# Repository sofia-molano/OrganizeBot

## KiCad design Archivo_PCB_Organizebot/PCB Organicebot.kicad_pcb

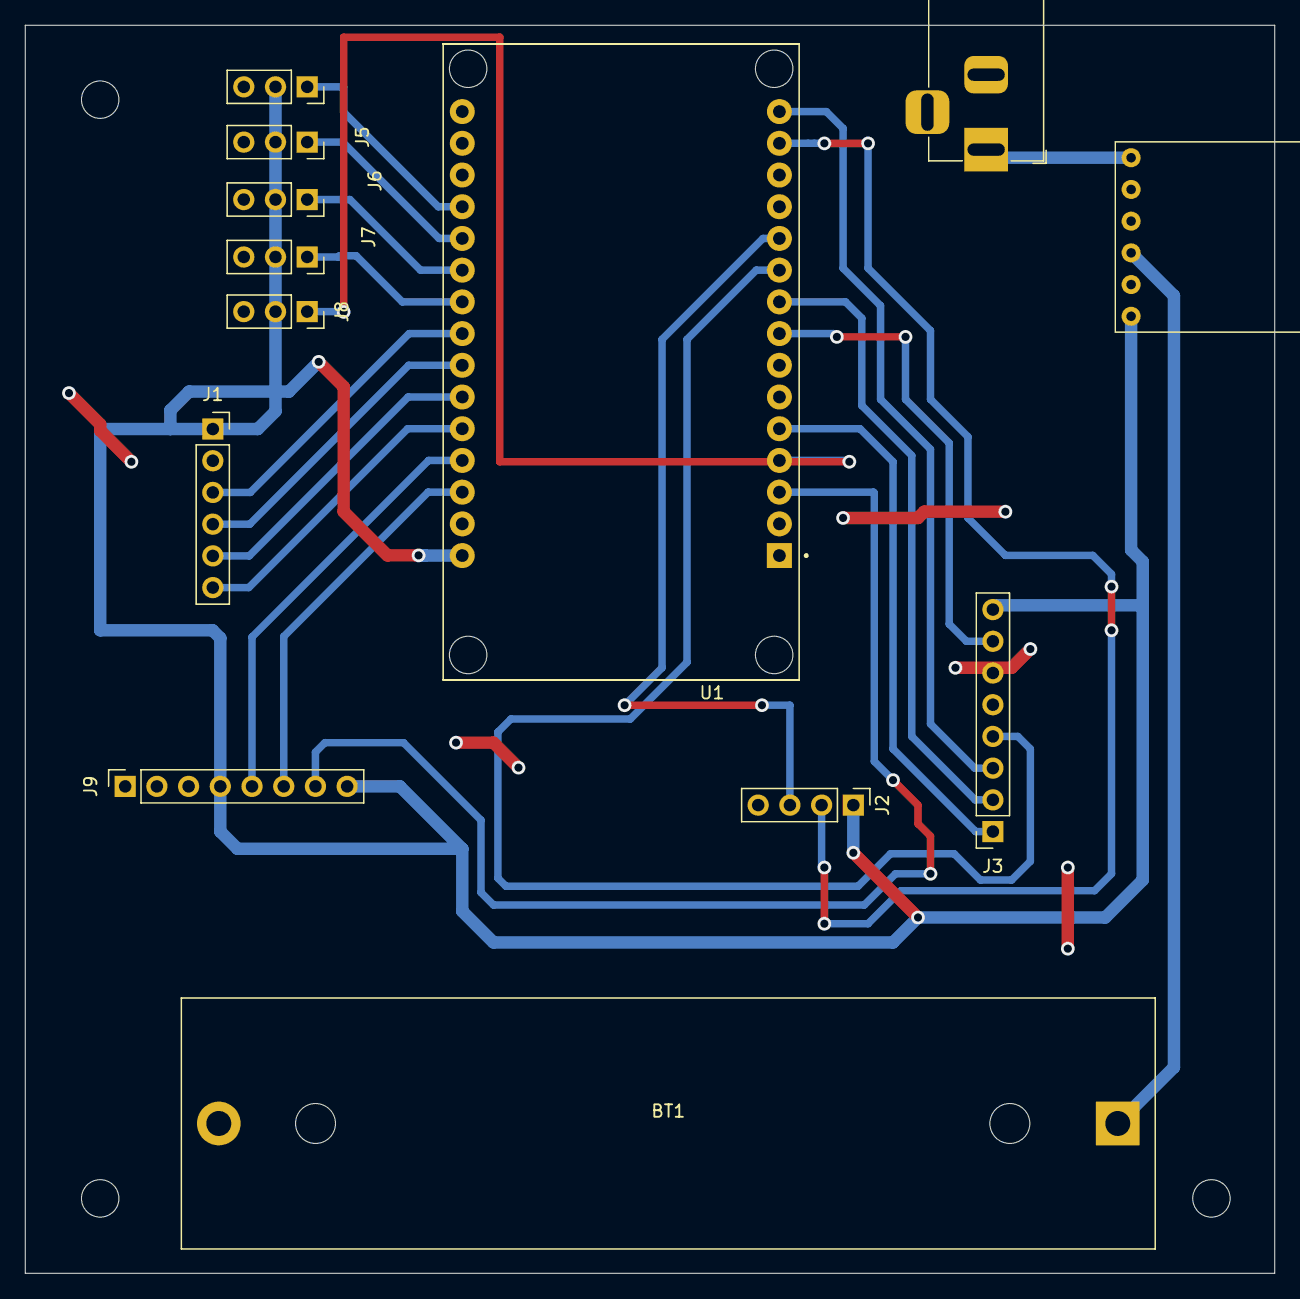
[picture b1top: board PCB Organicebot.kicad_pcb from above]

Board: 2 copper layers, 100.1 x 100.0 mm, 14 parts (0 on the bottom side), 23 nets.

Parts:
BT1: Battery; BatteryHolder_MPD_BH-18650-PC2
J1: Control Motor; PinSocket_1x06_P2.54mm_Vertical
J2: Ultrasonico HC SR04; PinHeader_1x04_P2.54mm_Vertical
J3: RFID; PinSocket_1x08_P2.54mm_Vertical
J4: Infrarojo 1; PinSocket_1x03_P2.54mm_Vertical
J5: Infrarojo 2; PinSocket_1x03_P2.54mm_Vertical
J6: Infrarojo 3; PinSocket_1x03_P2.54mm_Vertical
J7: Infrarojo 4; PinSocket_1x03_P2.54mm_Vertical
J8: Infrarojo 5; PinSocket_1x03_P2.54mm_Vertical
J9: COLOR TCS230; PinSocket_1x08_P2.54mm_Vertical
J14: Barrel_Jack_Switch; BarrelJack_Horizontal
Organizebot: MountingHole_3mm
U1: ESP32-DEVKIT-V1; MODULE_ESP32_DEVKIT_V1
U2: mh-cd42

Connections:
+5V: J1.1, J2.1, J3.8, J4.2, J5.2, J6.2, J7.2, J8.2, J9.4, J9.8, U1.30 (VIN), U2.6 (OUT-5V)
+BATT: BT1.1 (+), U2.4 (BAT)
/ECCO: J2.3, U1.11 (D21)
/IN1: J1.3, U1.23 (D25)
/IN2: J1.4, U1.24 (D26)
/IN3: J1.5, U1.25 (D27)
/IN4: J1.6, U1.26 (D14)
/MISO: J3.4, U1.10 (D19)
/MOSI: J3.3, U1.15 (D23)
/OUT: J9.7, U1.3 (D15)
/RESET: J3.7, U1.8 (D5)
/S2: J9.6, U1.28 (D13)
/S3: J9.5, U1.27 (D12)
/SCK: J3.2, U1.9 (D18)
/SDA: J3.1, U1.5 (D4)
/TRIGGER: J2.2, U1.14 (D22)
/i PWM 1: J4.1, U1.19 (D34)
/i PWM 2: J6.1, U1.21 (D32)
/i PWM 3: J5.1, U1.20 (D35)
/i PWM 4: J8.1, U1.4 (D2)
/i PWM 5: J7.1, U1.22 (D33)
GND: BT1.2 (-), J1.2, J2.4, J3.6, J4.3, J5.3, J6.3, J7.3, J8.3, J9.1, J14.2, J14.3, U1.2 (GND), U1.29 (GND), U2.2 (GND), U2.3 (GND), U2.5 (GND)
VDC: J14.1, U2.1 (VIN)

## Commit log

2024-09-25 PCB archives Organizebot
2024-09-25 Create Archives_PCB_Organizebot
2024-09-25 Archivo principal programacion ESP32
2024-09-25 Create Infrarroje_Ultrasonido.py
    Archivo funcional, detecta lineas y actua. Sobre linea blanca fondo negro.
2024-09-26 Create archivos_carcasa
2024-09-26 Create fotos_proyecto
2024-09-26 Create Archivo de texto
2024-09-26 Create Archivo_codigo_Principal
